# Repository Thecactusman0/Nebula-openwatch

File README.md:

# Nebula-openwatch
Nebula is a ESP32 based smartwatch proof of concept that features a rotating bezel encoder along with a suite of sensors and parts. This includes:

-ESP32-S3-MINI with wifi and bluetooth LE capabilities

-3 pushbuttons, 2 programmable

-I2C Ambient light sensor for automatic screen dimming

-Onboard lipo charging

-Onboard ldo regulator with voltage supervisor

-I2S amplifier for audio output (BLUETOOTH LE DOES NOT SUPPORT STREAMING AUDIO,CHANGES ARE NEEDED TO BOARD TO ENABLE USE OF THIS CHIP)

-I2S Mems microphone for  audio input(BLUETOOTH LE DOES NOT SUPPORT STREAMING AUDIO)

-I2C RTC module (HASNT BEEN SUFFICENTLY TESTED)

-Haptic vibration motor for user feedback

-4 pin dock connector (2.54 female header) for use with dock that provides serial programming and power.

-I2C 3 axis gyroscope and accelerometer

-200mah lipo battery

Total size is ~44mm diameter, ~12mm height

DO NOT BUILD PROOF OF CONCEPT FOR REFERENCE ONLY

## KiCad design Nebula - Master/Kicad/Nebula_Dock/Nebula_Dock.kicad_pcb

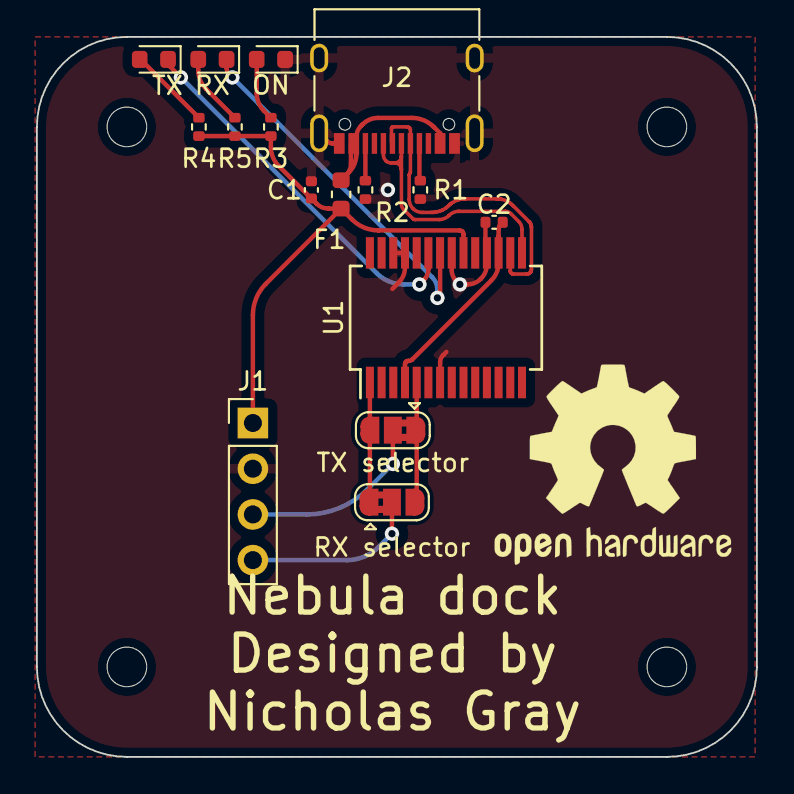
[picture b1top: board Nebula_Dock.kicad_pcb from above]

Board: 2 copper layers, 40.0 x 40.0 mm, 20 parts (0 on the bottom side), 17 nets.

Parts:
C1, C2: 0.1uF; C_0402_1005Metric
F1: Polyfuse; Fuse_0603_1608Metric
J1: Male_watch_connector; PinHeader_1x04_P2.54mm_Vertical
J2: USB_C_Receptacle_USB2.0; USB_C_Receptacle_XKB_U262-16XN-4BVC11
ON: STATUS; LED_0603_1608Metric
R1, R2: 5.1K; R_0402_1005Metric
R3, R4, R5: 270R; R_0402_1005Metric
REF1, REF2, REF3, REF4: MountingHole_2.2mm_M2
RX: RX_LED; LED_0603_1608Metric
RX selector: SolderJumper_3_Bridged12; SolderJumper-3_P1.3mm_Bridged2Bar12_RoundedPad1.0x1.5mm
TX: TX_LED; LED_0603_1608Metric
TX selector: SolderJumper_3_Bridged12; SolderJumper-3_P1.3mm_Bridged2Bar12_RoundedPad1.0x1.5mm
U1: FT232RL; SSOP-28_5.3x10.2mm_P0.65mm

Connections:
ESP_RX: J1.4, RX selector.2 (C)
ESP_TX: J1.3, TX selector.2 (C)
GND: C1.2, C2.2, J1.2, J2.A1 (GND), J2.A12 (GND), J2.B1 (GND), J2.B12 (GND), J2.S1 (SHIELD), ON.1 (K), R1.2, R2.1, U1.7 (GND), U1.18 (GND), U1.21 (GND), U1.25 (AGND), U1.26 (TEST)
unnamed: C2.1, U1.4 (VCCIO), U1.17 (3V3OUT)
unnamed: ON.2 (A), R3.2
unnamed: TX.1 (K), U1.23 (CBUS0)
unnamed: R4.2, TX.2 (A)
unnamed: RX.1 (K), U1.22 (CBUS1)
unnamed: R5.2, RX.2 (A)
unnamed: F1.1, J2.A4 (VBUS), J2.A9 (VBUS), J2.B4 (VBUS), J2.B9 (VBUS)
unnamed: J2.A5 (CC1), R1.1
unnamed: J2.B5 (CC2), R2.2
RX: RX selector.3 (B), TX selector.1 (A), U1.5 (RXD)
TX: RX selector.1 (A), TX selector.3 (B), U1.1 (TXD)
USB+: J2.A6 (D+), J2.B6 (D+), U1.15 (USBD+)
USB-: J2.A7 (D-), J2.B7 (D-), U1.16 (USBD-)
V_USB: C1.1, F1.2, J1.1, R3.1, R4.1, R5.1, U1.20 (VCC)

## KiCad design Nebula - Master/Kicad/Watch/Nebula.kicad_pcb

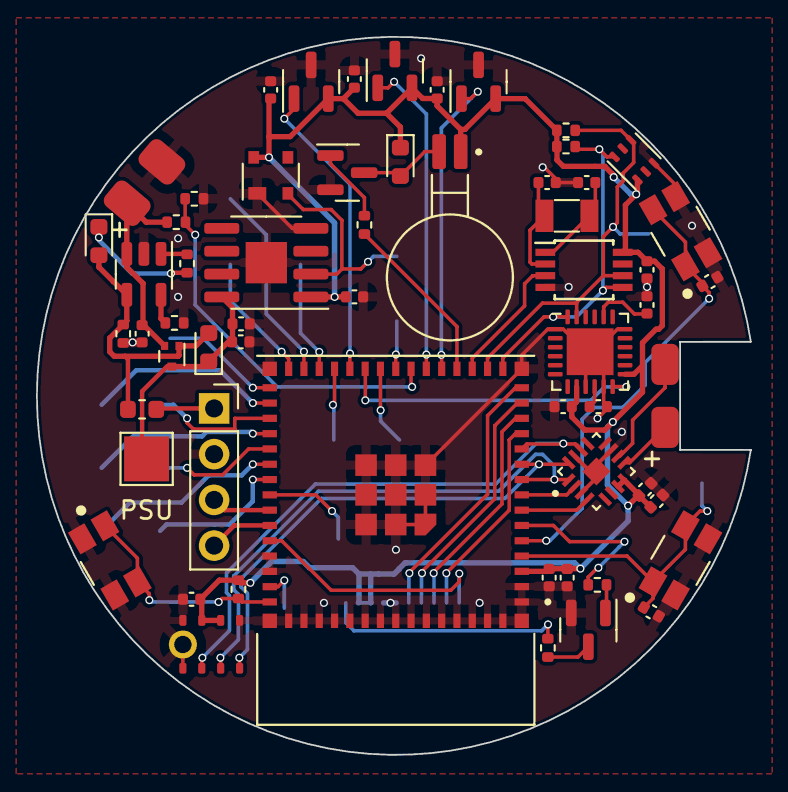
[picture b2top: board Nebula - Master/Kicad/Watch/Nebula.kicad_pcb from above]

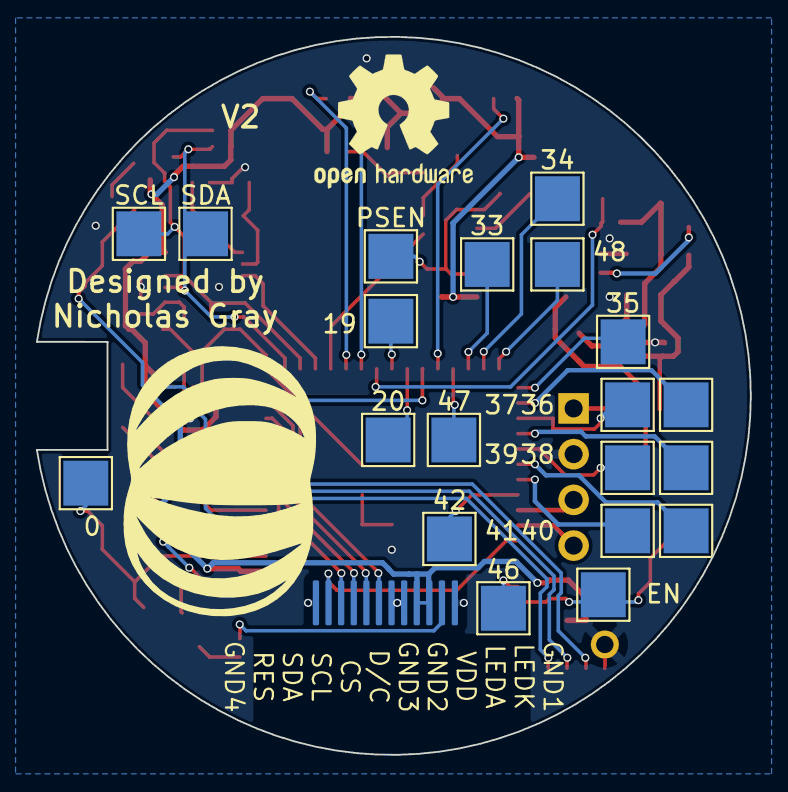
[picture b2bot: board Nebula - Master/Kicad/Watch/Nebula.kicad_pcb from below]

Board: 2 copper layers, 39.7 x 39.9 mm, 80 parts (22 on the bottom side), 61 nets.

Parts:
0, 19, 20, 33, 34, 35, 36, 37, 38, 39, 40, 41, 42, 46, 47, 48: TestPoint; TestPoint_Pad_2.5x2.5mm
BT1: Battery; Batt
C1, C2, C3, C5, C7, C8, C9, C16, C18, C20, C21: 0.1uF; C_0402_1005Metric
C4, C6, C11: 4.7uF; C_0402_1005Metric
C10: 22uF; C_0402_1005Metric
C12, C13: 12pF; C_0402_1005Metric
C15: 1uF; C_0402_1005Metric
C19: 22nF; C_0402_1005Metric
C22: 10uF; C_0402_1005Metric
D1: LED; LED_0603_1608Metric
D2, D3: SD0805S020S1R0; D_0603_1608Metric
EN: TestPoint; TestPoint_Pad_2.5x2.5mm
F1: Polyfuse; Fuse_0603_1608Metric
J1: Female dock; PinSocket_1x04_P2.54mm_Vertical
J2: Display; Circular Display connector
LS1: Speaker; Speaker6mm
M1: HMotor; XDCR_C0720B001F
PSEN: TestPoint; TestPoint_Pad_2.5x2.5mm
PSU: TestPoint; TestPoint_Pad_2.5x2.5mm
Q1, Q3: s8050; SOT-23
Q2: CJ3139K; SOT-723
R1: 5K; R_0402_1005Metric
R5: 442K; R_0402_1005Metric
R6: 160K; R_0402_1005Metric
R7: 470; R_0402_1005Metric
R10, R11: 1K; R_0402_1005Metric
R12: 10; R_0402_1005Metric
R13: 100K; R_0402_1005Metric
R20: 10k; R_0402_1005Metric
R21, R22: 4.7K; R_0402_1005Metric
SCL: TestPoint; TestPoint_Pad_2.5x2.5mm
SDA: TestPoint; TestPoint_Pad_2.5x2.5mm
SW1, SW2, SW3: SW_Push; SW_EVQ-P7J01P
U1, U2, U3: XC3202B183MR-G; SOT-23
U4: ESP32-S3-MINI-1-N8; XCVR_ESP32-S3-MINI-1-N8
U5: MCP73831T-2ATI/OT; SOT-23-5
U6: LTR-303ALS-01; Lite-On_LTR-303ALS-01
U7: LR1801G-33-SH2-R; HSOP-8-1EP_3.9x4.9mm_P1.27mm_EP2.3x2.3mm
U8: PCF8563TS; TSSOP-8_3x3mm_P0.65mm
U9: MAX98357AETE; QFN50P300X300X80-17N
U10: MPU6050; QFN-24-1EP_4x4mm_P0.5mm_EP2.6x2.6mm
U11: INMP441
U12: MAX811TEUS-T; SOT-143
Y1: 32.768KHz; Crystal_SMD_3215-2Pin_3.2x1.5mm

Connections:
+3V3: C1.1, C2.1, C3.1, C4.1, C8.2, C9.1, C10.1, C16.2, C20.2, C21.1, C22.1, D3.1 (K), J2.3, J2.4, M1.1 (+), R20.1, R21.1, R22.1, U1.2 (VCC), U2.2 (VCC), U3.2 (VCC), U4.3 (3V3), U6.1 (VDD), U7.1 (VOUT), U8.8 (VDD), U9.7 (VDD), U9.8 (VDD), U10.8 (VLOGIC), U10.13 (VDD), U11.7 (VDD), U11.8 (EN), U12.4 (VCC)
+BATT: BT1.1 (+), C6.1, Q2.2 (D), R5.1, U5.3 (VBAT)
BCLK/SCK: U4.10 (IO6), U9.16 (BCLK), U11.1 (SCK)
Battery: R5.2, R6.1, U4.22 (IO18)
CS: J2.8, U4.14 (IO10)
DC: J2.7, U4.15 (IO11)
DIN/SD: U4.9 (IO5), U9.1 (DIN), U11.2 (SD)
EN: EN.1, R20.2, SW1.1, U4.45 (EN)
ESP_RX: J1.4, U4.40 (RXD0)
ESP_TX: J1.3, U4.39 (TXD0)
GAIN: U4.8 (IO4), U9.2 (GAIN_SLOT)
GND: BT1.2 (-), C1.2, C2.2, C3.2, C4.2, C5.2, C6.2, C7.2, C8.1, C9.2, C10.2, C11.1, C12.1, C13.2, C15.2, C16.1, C18.2, C19.1, C20.1, C21.2, C22.2, J1.2, J2.1, J2.5, J2.6, J2.12, Q1.2 (E), Q3.2 (E), R1.1, R6.2, R13.1, SW1.2, SW2.2, SW3.2, U1.3 (GND), U2.3 (GND), U3.3 (GND), U4.1 (GND), U4.2 (GND), U4.42 (GND), U4.43 (GND), U4.46 (GND), U4.47 (GND), U4.48 (GND), U4.49 (GND), U4.50 (GND), U4.51 (GND), U4.52 (GND), U4.53 (GND), U4.54 (GND), U4.55 (GND), U4.56 (GND), U4.57 (GND), U4.58 (GND), U4.59 (GND), U4.60 (GND), U4.61 (GND), U4.61_1 (GND), U4.61_2 (GND), U4.61_3 (GND), U4.61_4 (GND), U4.61_5 (GND), U4.61_6 (GND), U4.61_7 (GND), U4.61_8 (GND), U4.62 (GND), U4.63 (GND), U4.64 (GND), U4.65 (GND), U5.2 (VSS), U6.3 (GND), U7.4 (GND), U8.4 (VSS), U9.3 (GND), U9.11 (GND), U9.15 (GND), U9.17 (EP), U10.1 (CLKIN), U10.9 (AD0), U10.11 (FYSNC), U10.18 (GND), U10.25 (EXP), U11.4 (L/R), U11.5 (GND), U11.6 (GND), U11.9 (GND), U12.1 (GND)
HES1: U1.1 (OUT), U4.26 (IO26)
HES2: U2.1 (OUT), U4.21 (IO17)
HES3: U3.1 (OUT), U4.20 (IO16)
HMotor: R11.1, U4.19 (IO15)
INT: U4.18 (IO14), U8.3 (~INT)
INT1: U4.25 (IO21), U10.12 (INT)
IO0: 0.1, C5.1, SW2.1, U4.4 (IO0)
IO1: C7.1, SW3.1, U4.5 (IO1)
LED: R10.1, U4.6 (IO2)
LRCLK/WS: U4.11 (IO7), U9.14 (LRCLK), U11.3 (WS)
MOSI: J2.10, U4.12 (IO8)
unnamed: C12.2, U8.1 (OSCI), Y1.2
unnamed: C13.1, U8.2 (OSCO), Y1.1
unnamed: C18.1, U10.10 (REGOUT)
unnamed: C19.2, U10.20 (CPOUT)
unnamed: D3.2 (A), M1.2 (-), Q3.3 (C)
unnamed: F1.2, J1.1
unnamed: J2.2, R12.2
unnamed: LS1.1, U9.10 (OUTN)
unnamed: LS1.2, U9.9 (OUTP)
unnamed: Q1.1 (B), R10.2
unnamed: Q1.3 (C), R12.1
unnamed: Q3.1 (B), R11.2
unnamed: R1.2, U5.5 (PROG)
unnamed: D1.1 (K), R7.2
unnamed: 33.1, U4.28 (IO33)
unnamed: 35.1, U4.31 (IO35)
unnamed: 19.1, U4.23 (IO19)
unnamed: 20.1, U4.24 (IO20)
unnamed: 34.1, U4.29 (IO34)
unnamed: 36.1, U4.32 (IO36)
unnamed: 37.1, U4.33 (IO37)
unnamed: 38.1, U4.34 (IO38)
unnamed: 39.1, U4.35 (IO39)
unnamed: 40.1, U4.36 (IO40)
unnamed: 41.1, U4.37 (IO41)
unnamed: 42.1, U4.38 (IO42)
unnamed: 46.1, U4.44 (IO46)
unnamed: 47.1, U4.27 (IO47)
unnamed: 48.1, U4.30 (IO48)
PSEN: PSEN.1, U7.2 (EN), U12.2 (~RESET)
PSU: C11.2, C15.1, D2.1 (K), PSU.1, Q2.3 (S), U7.8 (VIN)
RES: J2.11, U4.41 (IO45)
SCK: J2.9, U4.13 (IO9)
SCL: R21.2, SCL.1, U4.17 (IO13), U6.4 (SCL), U8.6 (SCL), U10.23 (SCL)
SD: U4.7 (IO3), U9.4 (SD_MODE)
SDA: R22.2, SDA.1, U4.16 (IO12), U6.6 (SDA), U8.5 (SDA), U10.24 (SDA)
STAT: R7.1, U5.1 (STAT)
VCC_IN: D1.2 (A), D2.2 (A), F1.1, Q2.1 (G), R13.2, U5.4 (VDD)

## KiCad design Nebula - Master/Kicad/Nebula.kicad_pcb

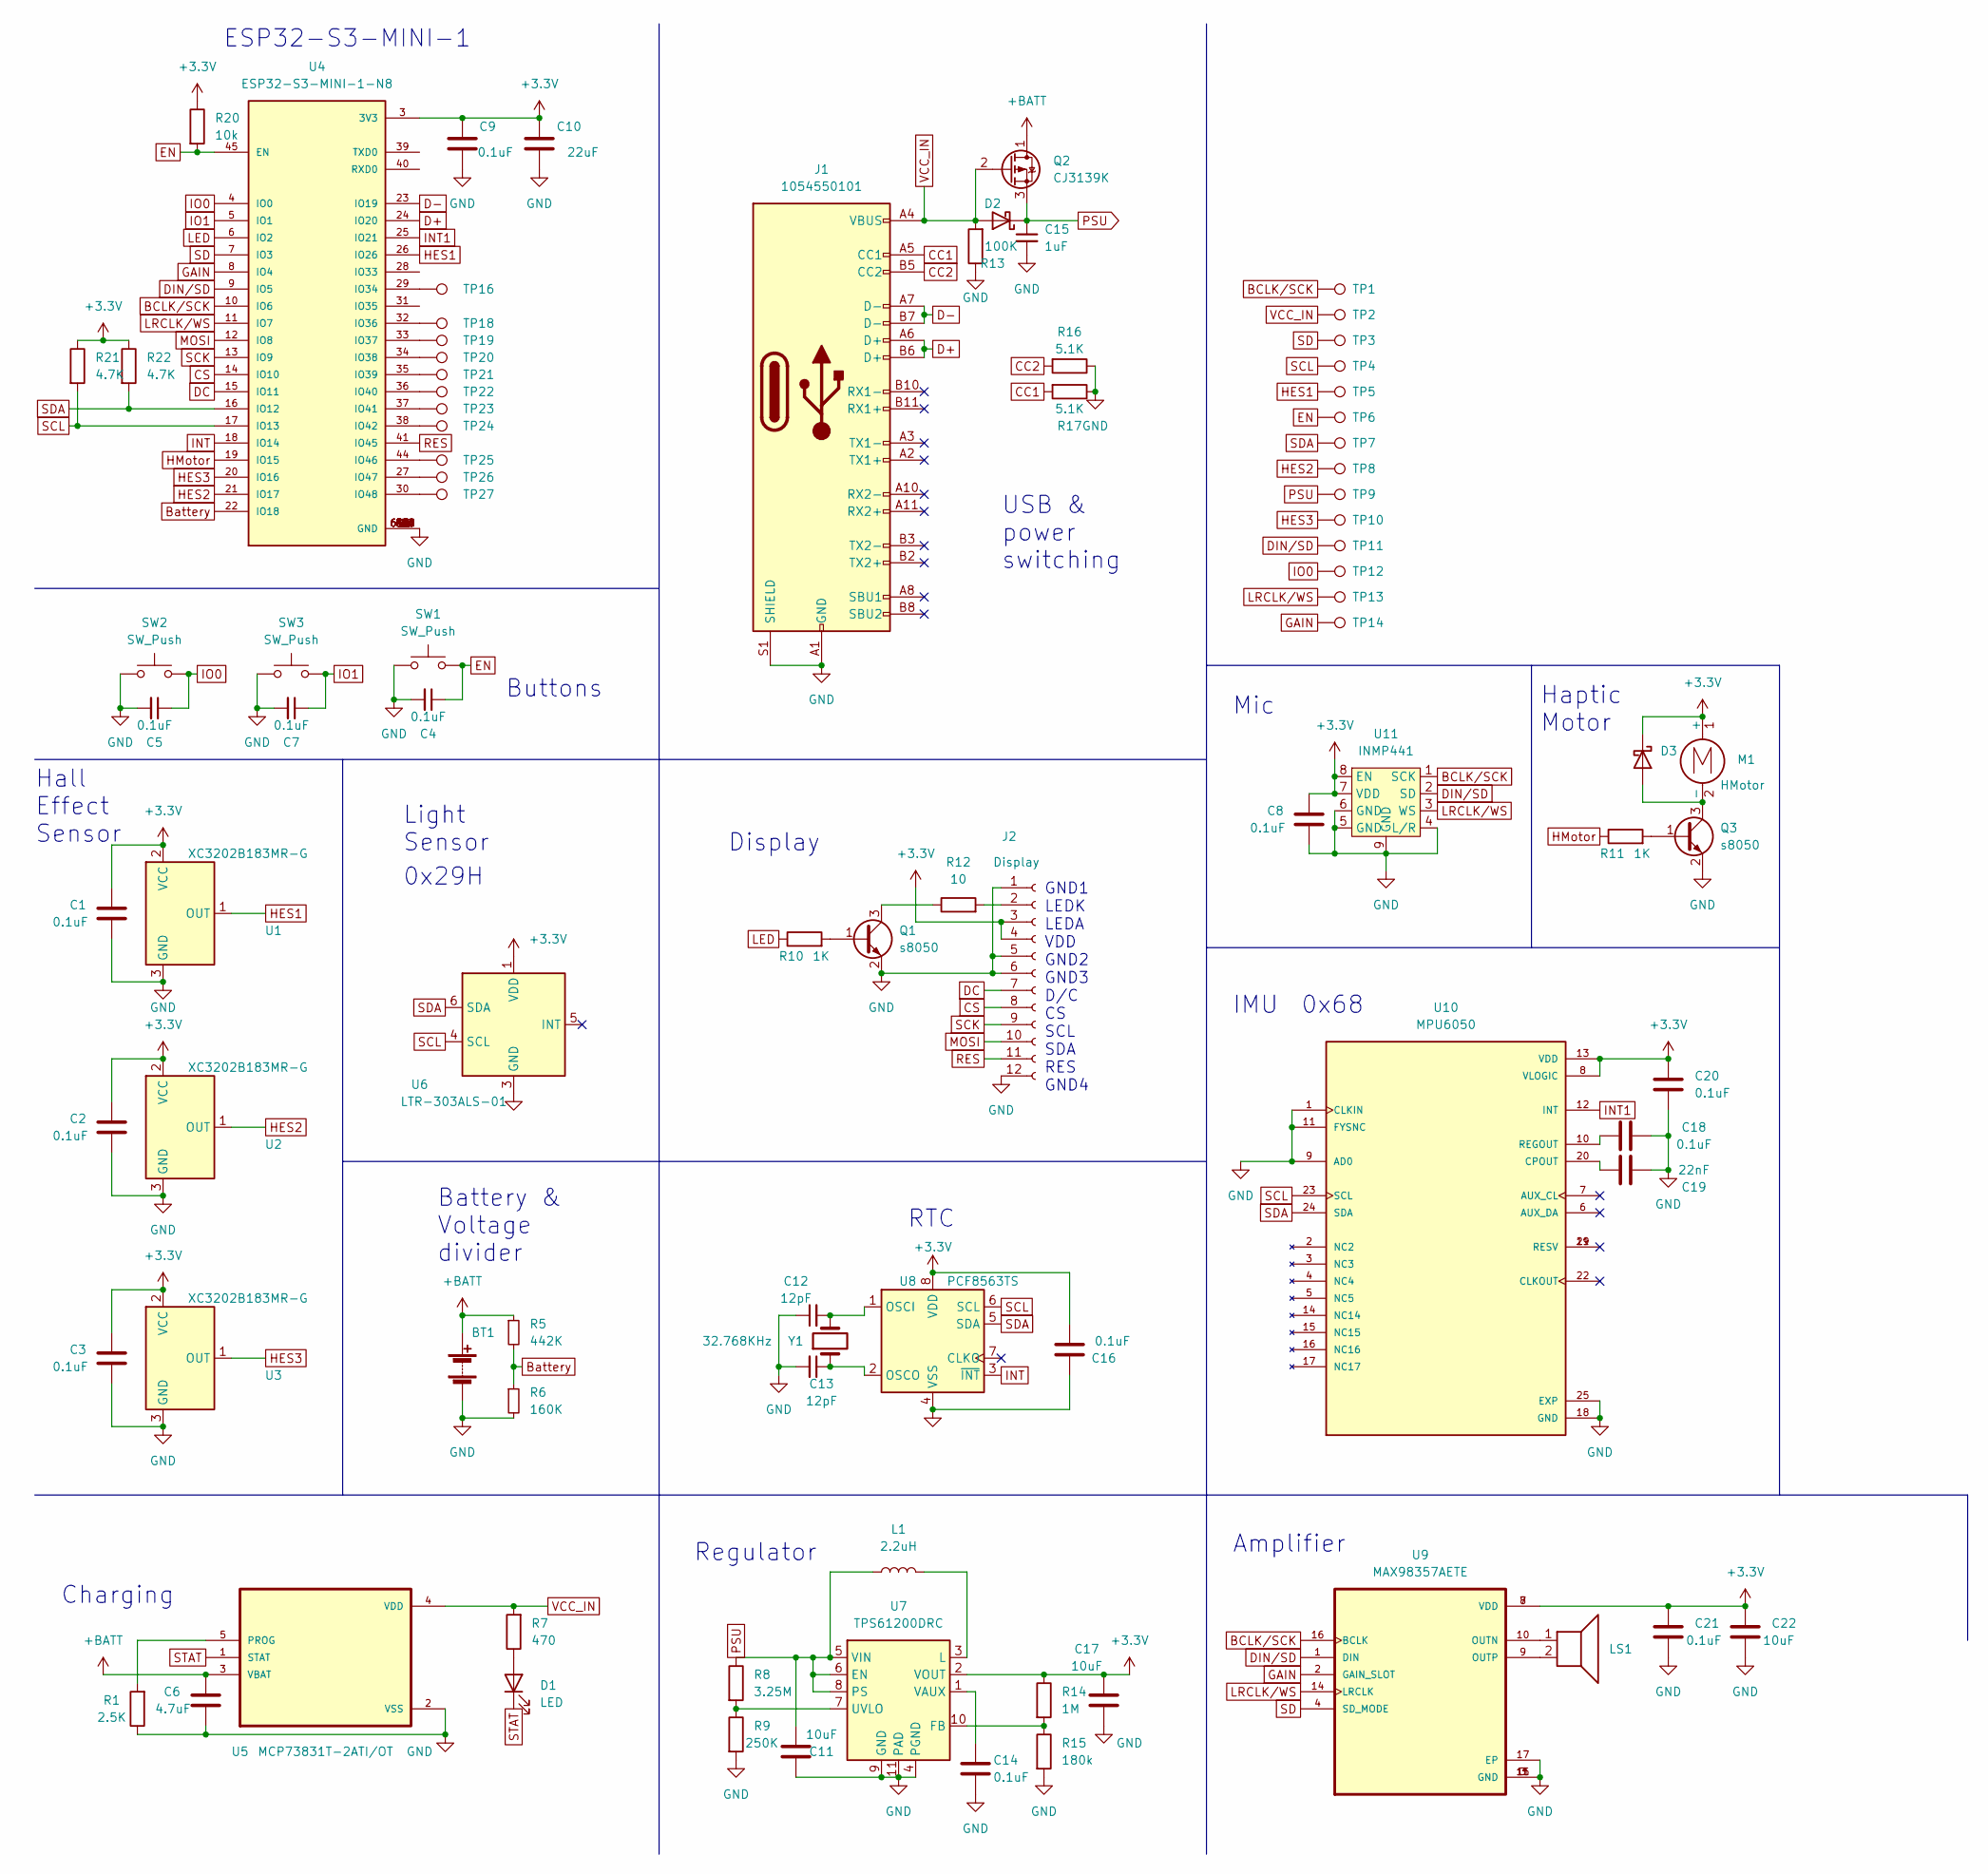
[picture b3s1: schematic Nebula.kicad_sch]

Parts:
BT1: Battery; Batt
C1, C2, C3, C4, C5, C7, C8, C9, C14, C16, C18, C20, C21: 0.1uF; C_0402_1005Metric; LCSC C123453
C6: 4.7uF; C_0402_1005Metric; LCSC C87147
C10: 22uF; C_0402_1005Metric; LCSC C415703
C11, C17, C22: 10uF; C_0402_1005Metric; LCSC C15525
C12: 12pF; C_0402_1005Metric
C13: 12pF; C_0402_1005Metric; LCSC C696888
C15: 1uF; C_0402_1005Metric; LCSC C14445
C19: 22nF; C_0402_1005Metric; LCSC C380305
D1: LED; LED_0603_1608Metric
D2, D3: SD0805S020S1R0; D_0603_1608Metric; LCSC C143773
J1: 1054550101; MOLEX_1054550101
J2: Display; Circular Display connector
L1: 2.2uH; L_1008_2520Metric_Pad1.43x2.20mm_HandSolder; LCSC C86092
LS1: Speaker; Speaker6mm
M1: HMotor; XDCR_C0720B001F; LCSC C2895081
Q1, Q3: s8050; SOT-23; LCSC C779775
Q2: CJ3139K; SOT-723; LCSC C70022
R1: 2.5K; R_0402_1005Metric; LCSC C2692758
R5: 442K; R_0402_1005Metric; LCSC C409854
R6: 160K; R_0402_1005Metric; LCSC C273339
R7: 470; R_0402_1005Metric; LCSC C284584
R8: 3.25M; R_0402_1005Metric; LCSC C227048
R9: 250K; R_0402_1005Metric; LCSC C2998084
R10, R11: 1K; R_0402_1005Metric; LCSC C242161
R12: 10; R_0402_1005Metric; LCSC C413044
R13: 100K; R_0402_1005Metric; LCSC C413017
R14: 1M; R_0402_1005Metric; LCSC C413126
R15: 180k; R_0402_1005Metric; LCSC C2909325
R16, R17: 5.1K; R_0402_1005Metric; LCSC C328327
R20: 10k; R_0402_1005Metric; LCSC C278577
R21, R22: 4.7K; R_0402_1005Metric; LCSC C2906869
SW1, SW2, SW3: SW_Push; SW_EVQ-P7J01P
TP1, TP2, TP3, TP4, TP5, TP6, TP7, TP8, TP9, TP10, TP11, TP12, TP13, TP14: TestPoint; TestPoint_Pad_2.5x2.5mm
TP16, TP18, TP19, TP20, TP21, TP22, TP23, TP24, TP25, TP26, TP27: TestPoint; TestPoint_Pad_1.5x1.5mm
U1, U2, U3: XC3202B183MR-G; SOT-23
U4: ESP32-S3-MINI-1-N8; XCVR_ESP32-S3-MINI-1-N8; PARTREV v0.6; LCSC C2913206
U5: MCP73831T-2ATI/OT; SOT-23-5; LCSC C14879
U6: LTR-303ALS-01; Lite-On_LTR-303ALS-01; LCSC C364577
U7: TPS61200DRC; Texas_S-PVSON-N10_ThermalVias; LCSC C140320
U8: PCF8563TS; SON50P300X300X100-11N
U9: MAX98357AETE; QFN50P300X300X80-17N; LCSC C910544
U10: MPU6050; QFN-24-1EP_4x4mm_P0.5mm_EP2.6x2.6mm; PARTREV 3.4
U11: INMP441
Y1: 32.768KHz; Crystal_SMD_3215-2Pin_3.2x1.5mm; LCSC C383844

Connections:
+3V3: C1.1, C2.1, C3.1, C8.2, C9.1, C10.1, C16.2, C17.2, C20.2, C21.1, C22.1, D3.1 (K), J2.3, J2.4, M1.1 (+), R14.1, R20.1, R21.1, R22.1, U1.2 (VCC), U2.2 (VCC), U3.2 (VCC), U4.3 (3V3), U6.1 (VDD), U7.2 (VOUT), U8.8 (VDD), U9.7 (VDD), U9.8 (VDD), U10.8 (VLOGIC), U10.13 (VDD), U11.7 (VDD), U11.8 (EN)
+BATT: BT1.1 (+), C6.1, Q2.1 (D), R5.1, U5.3 (VBAT)
BCLK/SCK: TP1.1, U4.10 (IO6), U9.16 (BCLK), U11.1 (SCK)
Battery: R5.2, R6.1, U4.22 (IO18)
CC1: J1.A5 (CC1), R17.2
CC2: J1.B5 (CC2), R16.2
CS: J2.8, U4.14 (IO10)
D+: J1.A6 (D+), J1.B6 (D+), U4.24 (IO20)
D-: J1.A7 (D-), J1.B7 (D-), U4.23 (IO19)
DC: J2.7, U4.15 (IO11)
DIN/SD: TP11.1, U4.9 (IO5), U9.1 (DIN), U11.2 (SD)
EN: C4.1, R20.2, SW1.1, TP6.1, U4.45 (EN)
GAIN: TP14.1, U4.8 (IO4), U9.2 (GAIN_SLOT)
GND: BT1.2 (-), C1.2, C2.2, C3.2, C4.2, C5.2, C6.2, C7.2, C8.1, C9.2, C10.2, C11.1, C12.1, C13.2, C14.2, C15.2, C16.1, C17.1, C18.2, C19.1, C20.1, C21.2, C22.2, J1.A1 (GND), J1.A12 (GND), J1.B1 (GND), J1.B12 (GND), J1.S1 (SHIELD), J2.1, J2.5, J2.6, J2.12, Q1.2 (E), Q3.2 (E), R1.1, R6.2, R9.2, R13.1, R15.2, R16.1, R17.1, SW1.2, SW2.2, SW3.2, U1.3 (GND), U2.3 (GND), U3.3 (GND), U4.1 (GND), U4.2 (GND), U4.42 (GND), U4.43 (GND), U4.46 (GND), U4.47 (GND), U4.48 (GND), U4.49 (GND), U4.50 (GND), U4.51 (GND), U4.52 (GND), U4.53 (GND), U4.54 (GND), U4.55 (GND), U4.56 (GND), U4.57 (GND), U4.58 (GND), U4.59 (GND), U4.60 (GND), U4.61 (GND), U4.61_1 (GND), U4.61_2 (GND), U4.61_3 (GND), U4.61_4 (GND), U4.61_5 (GND), U4.61_6 (GND), U4.61_7 (GND), U4.61_8 (GND), U4.62 (GND), U4.63 (GND), U4.64 (GND), U4.65 (GND), U5.2 (VSS), U6.3 (GND), U7.4 (PGND), U7.9 (GND), U7.11 (PAD), U8.4 (VSS), U9.3 (GND), U9.11 (GND), U9.15 (GND), U9.17 (EP), U10.1 (CLKIN), U10.9 (AD0), U10.11 (FYSNC), U10.18 (GND), U10.25 (EXP), U11.4 (L/R), U11.5 (GND), U11.6 (GND), U11.9 (GND)
HES1: TP5.1, U1.1 (OUT), U4.26 (IO26)
HES2: TP8.1, U2.1 (OUT), U4.21 (IO17)
HES3: TP10.1, U3.1 (OUT), U4.20 (IO16)
HMotor: R11.1, U4.19 (IO15)
INT: U4.18 (IO14), U8.3 (~INT)
INT1: U4.25 (IO21), U10.12 (INT)
IO0: C5.1, SW2.1, TP12.1, U4.4 (IO0)
IO1: C7.1, SW3.1, U4.5 (IO1)
LED: R10.1, U4.6 (IO2)
LRCLK/WS: TP13.1, U4.11 (IO7), U9.14 (LRCLK), U11.3 (WS)
MOSI: J2.10, U4.12 (IO8)
unnamed: C12.2, U8.1 (OSCI), Y1.2
unnamed: C13.1, U8.2 (OSCO), Y1.1
unnamed: C14.1, U7.1 (VAUX)
unnamed: C18.1, U10.10 (REGOUT)
unnamed: C19.2, U10.20 (CPOUT)
unnamed: D1.2 (A), R7.1
unnamed: D3.2 (A), M1.2 (-), Q3.3 (C)
unnamed: J2.2, R12.2
unnamed: L1.2, U7.3 (L)
unnamed: LS1.1, U9.10 (OUTN)
unnamed: LS1.2, U9.9 (OUTP)
unnamed: Q1.1 (B), R10.2
unnamed: Q1.3 (C), R12.1
unnamed: Q3.1 (B), R11.2
unnamed: R1.2, U5.5 (PROG)
unnamed: R8.2, R9.1, U7.7 (UVLO)
unnamed: R14.2, R15.1, U7.10 (FB)
unnamed: TP16.1, U4.29 (IO34)
unnamed: TP18.1, U4.32 (IO36)
unnamed: TP19.1, U4.33 (IO37)
unnamed: TP20.1, U4.34 (IO38)
unnamed: TP21.1, U4.35 (IO39)
unnamed: TP22.1, U4.36 (IO40)
unnamed: TP23.1, U4.37 (IO41)
unnamed: TP24.1, U4.38 (IO42)
unnamed: TP25.1, U4.44 (IO46)
unnamed: TP26.1, U4.27 (IO47)
unnamed: TP27.1, U4.30 (IO48)
PSU: C11.2, C15.1, D2.1 (K), L1.1, Q2.3 (S), R8.1, TP9.1, U7.5 (VIN), U7.6 (EN), U7.8 (PS)
RES: J2.11, U4.41 (IO45)
SCK: J2.9, U4.13 (IO9)
SCL: R21.2, TP4.1, U4.17 (IO13), U6.4 (SCL), U8.6 (SCL), U10.23 (SCL)
SD: TP3.1, U4.7 (IO3), U9.4 (SD_MODE)
SDA: R22.2, TP7.1, U4.16 (IO12), U6.6 (SDA), U8.5 (SDA), U10.24 (SDA)
STAT: D1.1 (K), U5.1 (STAT)
VCC_IN: D2.2 (A), J1.A4 (VBUS), J1.A9 (VBUS), J1.B4 (VBUS), J1.B9 (VBUS), Q2.2 (G), R7.2, R13.2, TP2.1, U5.4 (VDD)

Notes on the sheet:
0x68
Regulator
Hall Effect Sensor
Charging
GND1 LEDK LEDA VDD GND2 GND3 D/C CS SCL SDA RES GND4
Haptic Motor
Amplifier
Display
USB & power switching
ESP32-S3-MINI-1
Mic
Light Sensor
IMU
0x29H
Buttons
Battery & Voltage divider
RTC

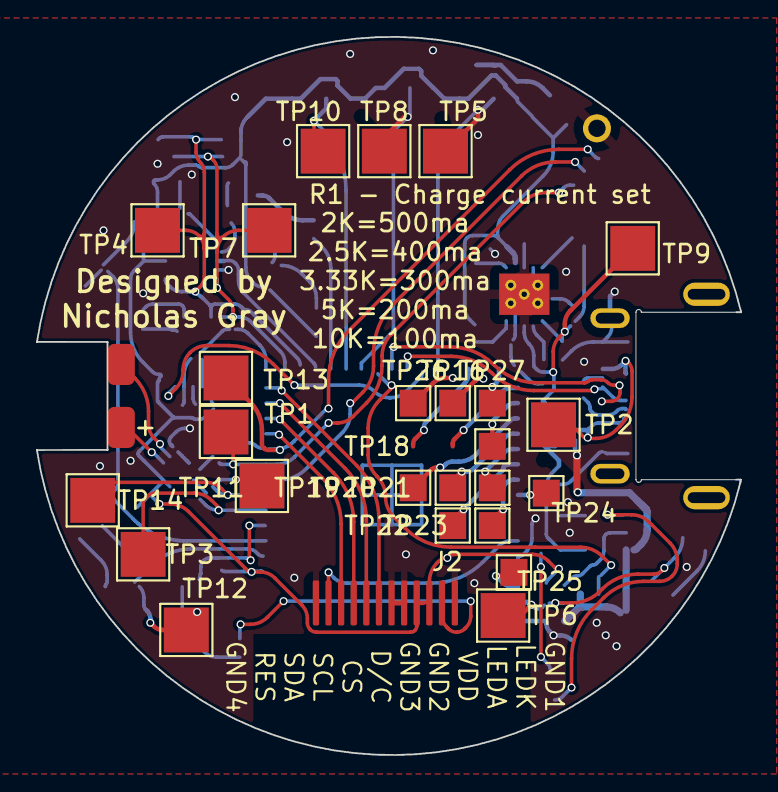
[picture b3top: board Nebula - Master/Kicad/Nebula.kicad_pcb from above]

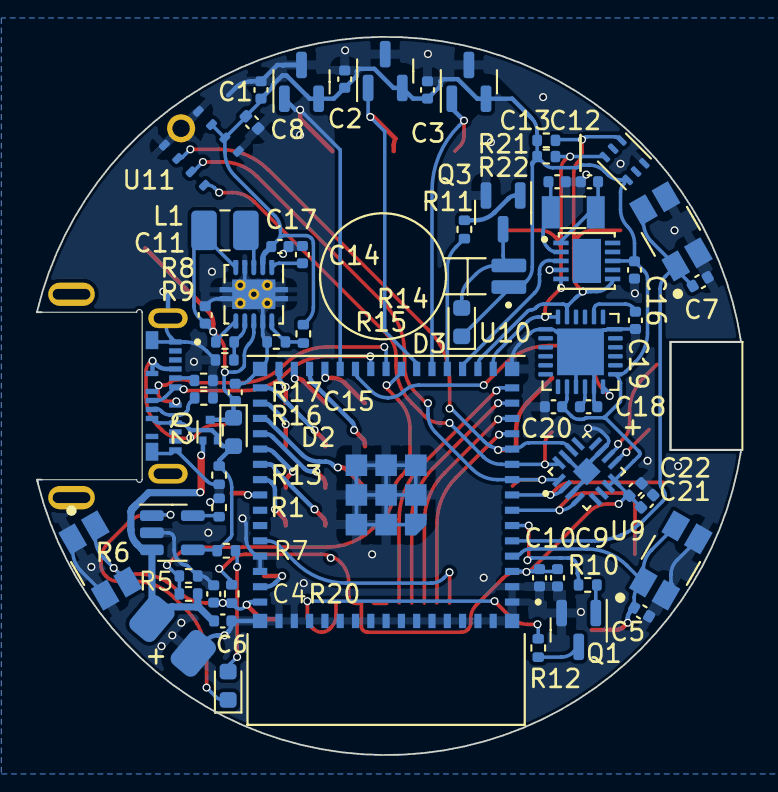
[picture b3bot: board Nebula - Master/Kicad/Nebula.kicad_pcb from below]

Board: 2 copper layers, 39.1 x 39.9 mm, 91 parts (65 on the bottom side), 61 nets.

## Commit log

2022-09-09 Naming Fix
2022-09-09 gerber update
2022-09-13 Removed old gerbers
2022-09-17 Added BOM and minor changes
    Fixed mosfet footprint and magnetic sensor footprints
2022-10-09 Secondary version
    Upgraded power system with ldo and voltage supervisor.
    Changed some footprints to make more accessible.
    Increased test point size.
    Removed onboard usb c connector and moved to dock assembly, onboard usb c will hopefully return in the next version.
    Fixed problems with io0 holding low.
    Increased power trace thickness.
2022-10-10 Added pcb images, schematic pdf and step
2022-10-15 changed prgm pin on dock
2023-01-18 3d files
2023-01-18 Code
